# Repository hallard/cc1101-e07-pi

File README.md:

# CC1101 E07 Shield for Raspberry PI

This shield is used to hold [CC1101][1] Transceiver module with Raspbery PI. As soon as pinout is the same it should also works with 868 and/or 915 modules. You can easily find theese modules on Aliexpress.

It has just few minimal features, it has been created to be used for [Cyble RF 433Mhz][4] everblue reading water meter in France.

This shield can also act as a RF transceiver according already made or custom made software.    

## Features

**Version 1.0**

- Placement for E07-CC1101S 433MHz module
- Placement for choosing single Wire, SMA or u-FL Antenna type
- 3 x LED for visual indication

I received V1.0 boards from JLCPCB, they are working fine and as expected.

## Schematics

SPI connexion is classic (MOSI/MISO/CLK), Chip Select is connected to CE0.

```
Raspberry PI         CC1101 Module 
   GPIO22  <---->  GDO2 (unused in code)
   GPIO25  <---->  GDO0

Raspberry PI      On Board LEDS
   GPIO23  <---->  LED1 (Red)
   GPIO24  <---->  LED2 (Green)
   GPIO7   <---->  LED3 (Blue)
```

## Assembled boards

## Connected to Raspberry PI

## Antenna Option

You can connect different antenna with all theese option, Spring, uFL, SMA or even 17cm wire.

## Software

I added some changes to the original firmware (Led, Scan, Frequency select, ...) and published on my github [everblu-meters-pi][6].
Should run out of the box with this board (including leds control), just plug, and play.

All credits to original code (but also **all the hard work** to get things working) are from [here][4] then exposed to github [here][5].

## License

This work is licensed under a [Creative Commons Attribution-NonCommercial-ShareAlike 4.0 International License](https://creativecommons.org/licenses/by-nc-sa/4.0/).
If you want to do commercial stuff with this project, please contact [CH2i company](https://ch2i.eu/en#support) so we can organize an simple agreement.

## Lazy building your own? 

I've put some of these board on [tindie][7], so you can order one (EU only) from my [store][7]. They are also available on [Lectronz](https://lectronz.com/products/cc1101-pi).

European customers may prefer ordering on Lectronz, which offers additional payment methods and pricing in Euros.

## Misc

See news and other projects on my [blog][2] 

[1]: https://www.cdebyte.com/products/E07-M1101S
[2]: https://hallard.me
[3]: https://oshpark.com/shared_projects/BVwV2j3b
[4]: http://www.lamaisonsimon.fr/wiki/doku.php?id=maison2:compteur_d_eau:compteur_d_eau
[5]: https://github.com/neutrinus/everblu-meters
[6]: https://github.com/hallard/everblu-meters-pi
[7]: https://www.tindie.com/products/hallard/cc1101-mini-shield-for-raspberry-pi

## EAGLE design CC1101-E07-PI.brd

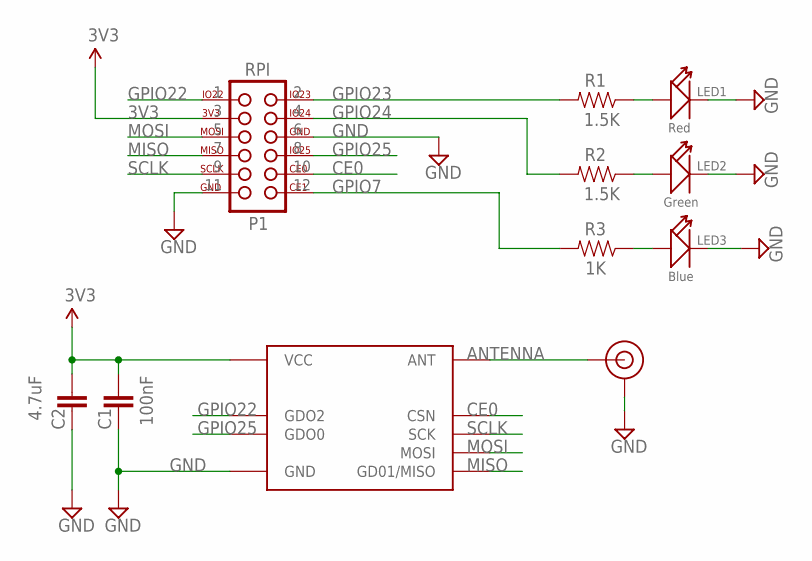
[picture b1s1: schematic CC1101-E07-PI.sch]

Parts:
C1: 100nF; 0402-CAP
C2: 4.7uF; 0402-CAP
J1: 2X6_BOTTOM; 2X06
J$1: ANTENNASMA; SMA_PAD
LED1: Red; LED-0402
LED2: Green; LED-0402
LED3: Blue; LED-0402
R1, R2: 1.5K; 0402-RES
R3: 1K; 0402-RES
U1: E07-400M10S; E07-900M10S

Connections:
3V3: C1.2, C2.2, J1.3 (17), U1.9 (VCC)
ANTENNA: J$1.ANT0 (ANT), J$1.ANT1 (ANT), J$1.ANT2 (ANT), U1.21 (ANT)
CE0: J1.10 (24), U1.19 (CSN)
GND: C1.1, C2.1, J1.6 (20), J1.11 (25), J$1.GND3 (GND), J$1.GND4 (GND), J$1.GND5 (GND), J$1.GND6 (GND), LED1.-, LED2.-, LED3.-, U1.1 (GND), U1.2 (GND), U1.3 (GND), U1.4 (GND), U1.5 (GND), U1.11 (GND), U1.12 (GND), U1.20 (GND), U1.22 (GND)
GPIO7: J1.12 (26), R3.2
GPIO22: J1.1 (15), U1.14 (GDO2)
GPIO23: J1.2 (16), R1.2
GPIO24: J1.4 (18), R2.2
GPIO25: J1.8 (22), U1.15 (GDO0)
MISO: J1.7 (21), U1.16 (GD01/MISO)
MOSI: J1.5 (19), U1.17 (MOSI)
unnamed: LED1.+, R1.1
unnamed: LED2.+, R2.1
unnamed: LED3.+, R3.1
SCLK: J1.9 (23), U1.18 (SCK)

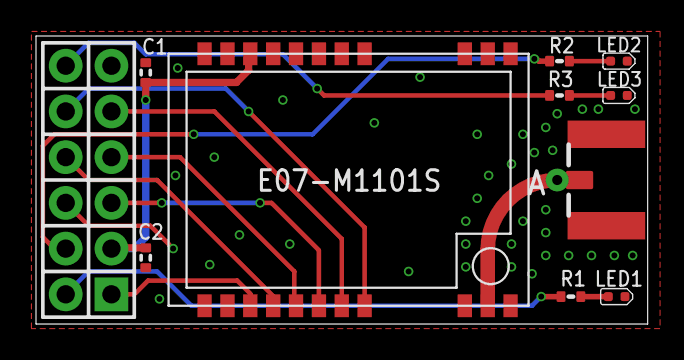
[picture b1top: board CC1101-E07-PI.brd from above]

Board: 2 copper layers, 34.0 x 16.0 mm, 11 parts (0 on the bottom side), 15 nets.

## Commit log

2023-07-14 fix links
2023-07-14 fixed schematics
2023-07-14 Changed Title
2023-07-15 added tindie link
2023-07-15 fixed wrong filename
2026-04-26 docs: add Lectronz badges next to Tindie
2026-04-29 Add CC BY-NC-SA 4.0 LICENSE and align README
2026-04-29 license: use pure CC BY-NC-SA 4.0 text for GitHub auto-detection
2026-04-29 license: add copyright header above CC BY-NC-SA 4.0 text

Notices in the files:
parts and their libraries:
SparkFun-Aesthetics: Licensing: Creative Commons ShareAlike 4.0 International - https://creativecommons.org/licenses/by-sa/4.0
